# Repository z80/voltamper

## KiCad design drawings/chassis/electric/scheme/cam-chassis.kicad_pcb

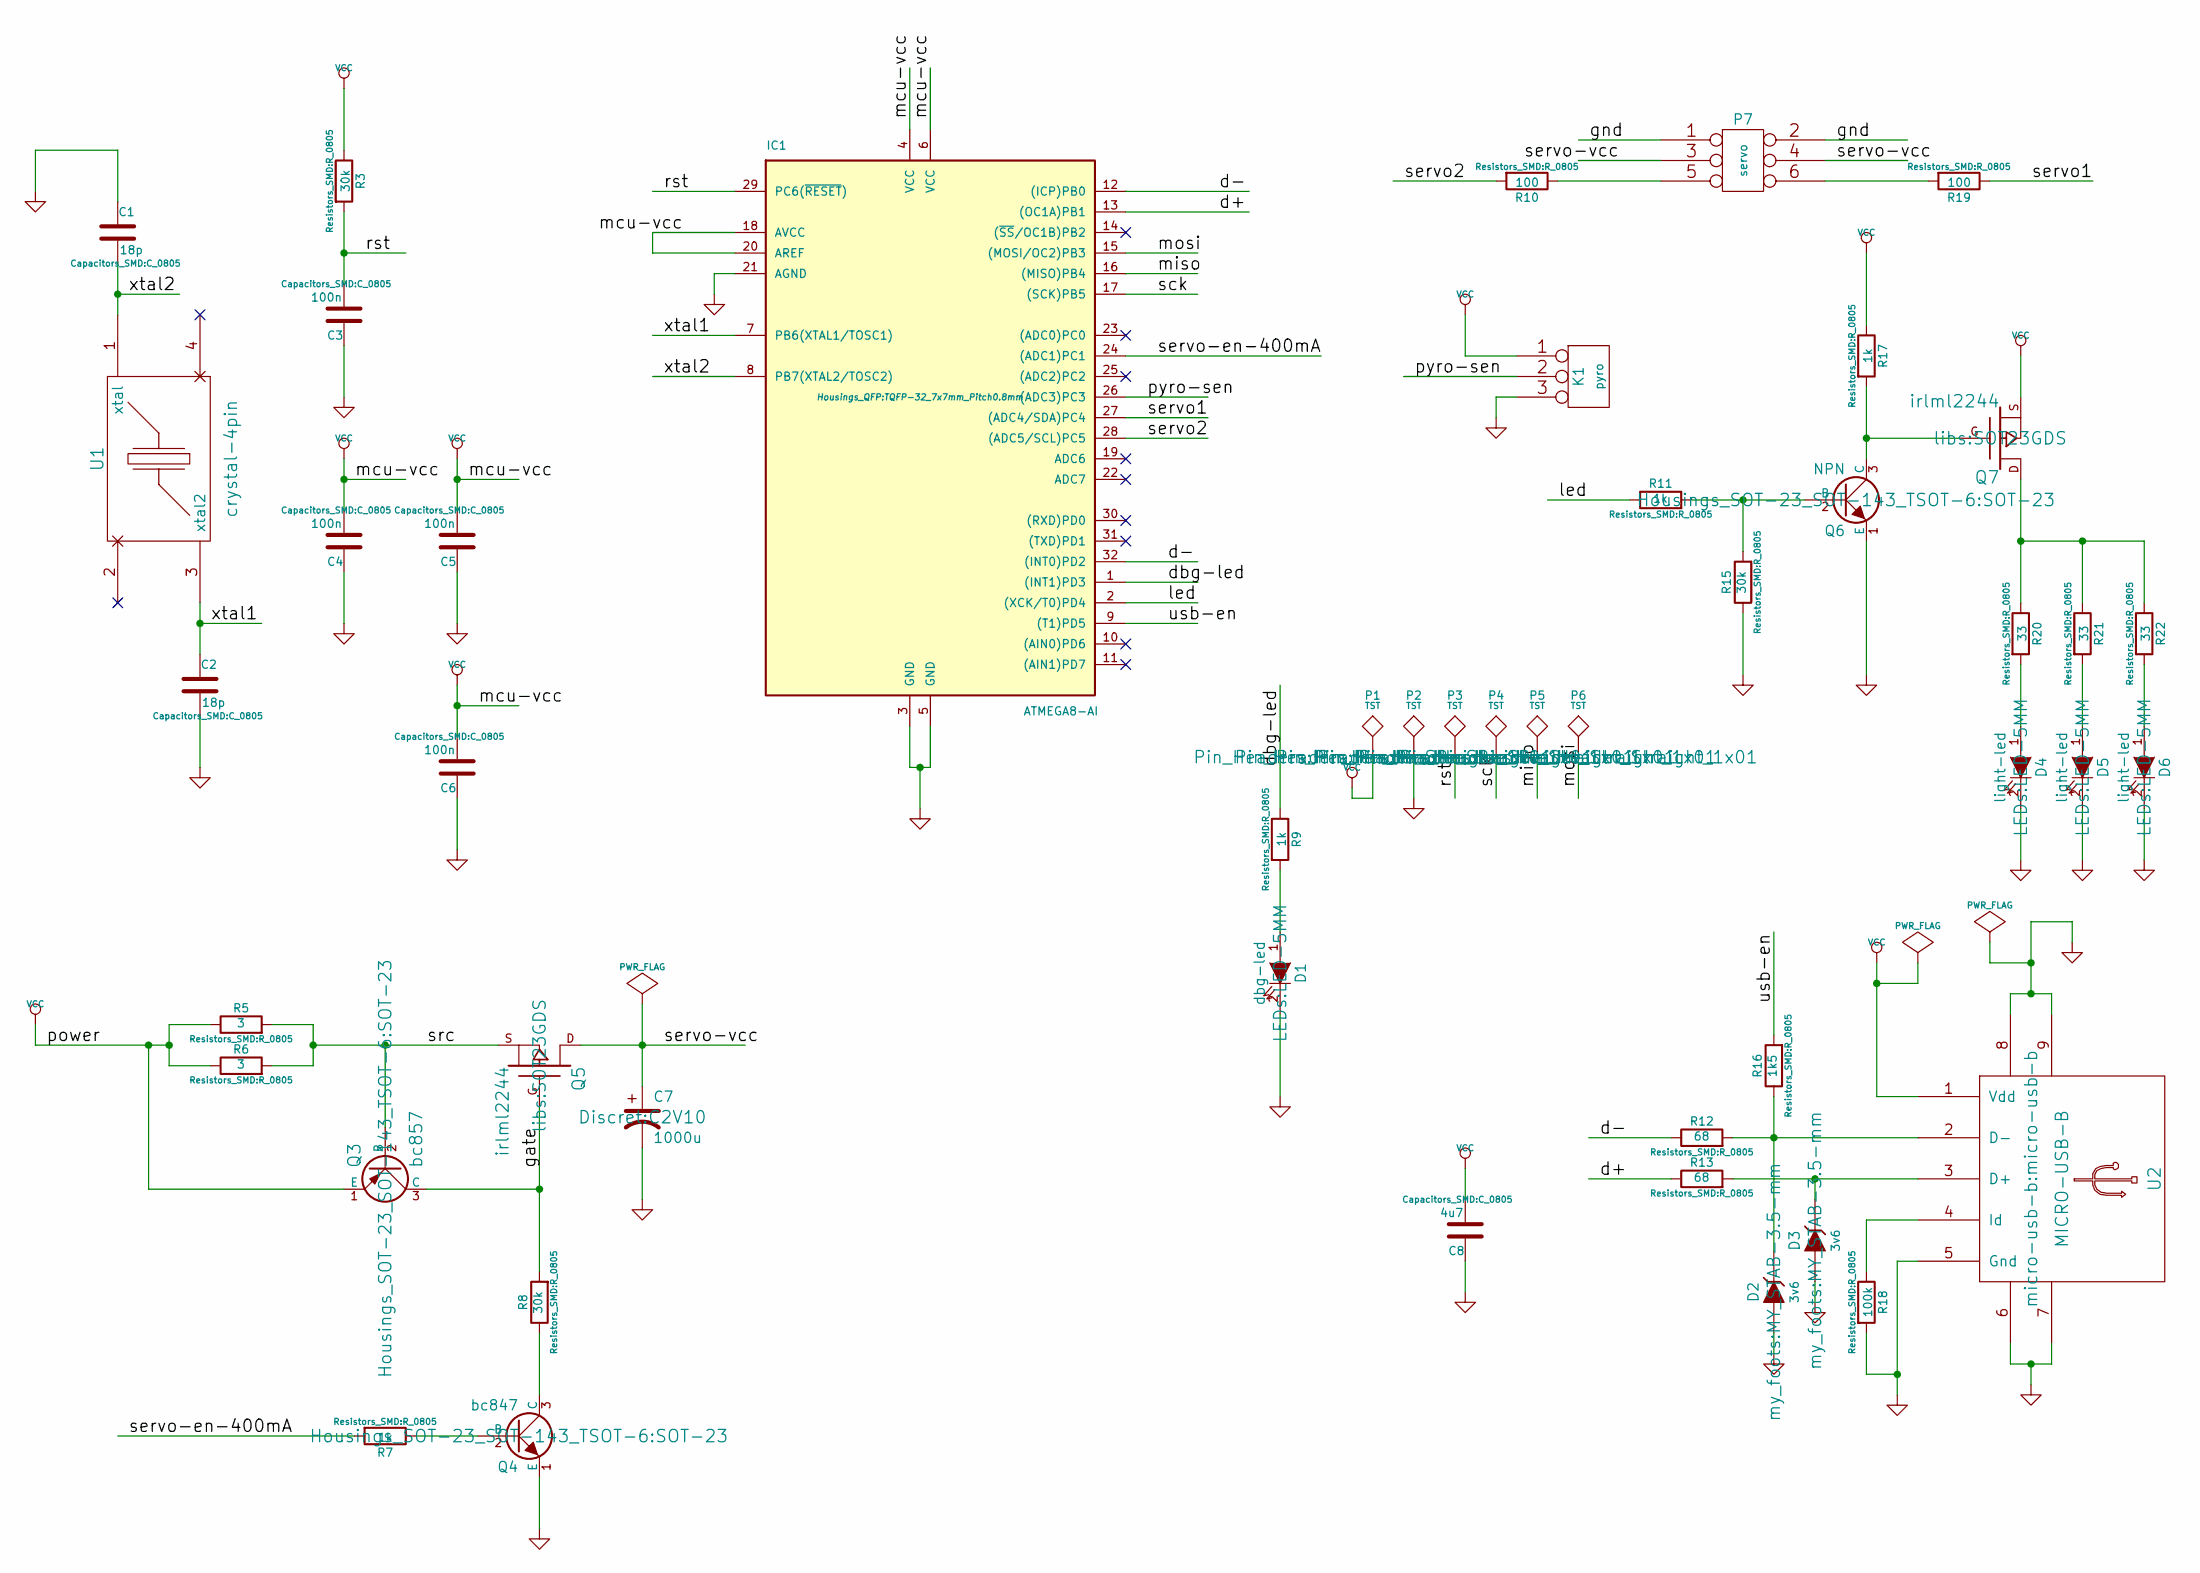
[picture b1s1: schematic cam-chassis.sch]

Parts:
C1, C2: 18p; C_0805
C3, C4, C5, C6: 100n; C_0805
C7: 1000u; C2V10
C8: 4u7; C_0805
D1: dbg-led; LED-5MM
D2, D3: 3v6; MY_STAB-3.5-mm
D4, D5, D6: light-led; LED-5MM
IC1: ATMEGA8-AI; TQFP-32_7x7mm_Pitch0.8mm
K1: pyro; Pin_Header_Straight_1x03
P1, P2, P3, P4, P5, P6: TST; Pin_Header_Straight_1x01
P7: servo; Pin_Header_Straight_2x03
Q3: bc857; SOT-23
Q4: bc847; SOT-23
Q5, Q7: irlml2244; SOT23GDS
Q6: NPN; SOT-23
R3, R8, R15: 30k; R_0805
R5, R6: 3; R_0805
R7, R9, R11, R17: 1k; R_0805
R10, R19: 100; R_0805
R12, R13: 68; R_0805
R16: 1k5; R_0805
R18: 100k; R_0805
R20, R21, R22: 33; R_0805
U1: crystal-4pin; CRYSTAL-SMD-5x3
U2: MICRO-USB-B; micro-usb-b

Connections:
/d+: IC1.13 ((OC1A)PB1), R13.1
/d-: IC1.12 ((ICP)PB0), IC1.32 ((INT0)PD2), R12.1
/dbg-led: IC1.1 ((INT1)PD3), R9.1
/gate: Q3.3 (C), Q5.G, R8.2
/led: IC1.2 ((XCK/T0)PD4), R11.1
/miso: IC1.16 ((MISO)PB4), P5.1
/mosi: IC1.15 ((MOSI/OC2)PB3), P6.1
/pyro-sen: IC1.26 ((ADC3)PC3), K1.2 (PM)
/rst: C3.2, IC1.29 (PC6(~RESET~)), P3.1, R3.2
/sck: IC1.17 ((SCK)PB5), P4.1
/servo1: IC1.27 ((ADC4/SDA)PC4), R19.1
/servo2: IC1.28 ((ADC5/SCL)PC5), R10.2
/servo-en-400mA: IC1.24 ((ADC1)PC1), R7.2
/servo-vcc: C7.1, P7.3, P7.4, Q5.D
/src: Q3.2 (B), Q5.S, R5.2, R6.2
/usb-en: IC1.9 ((T1)PD5), R16.2
/xtal1: C2.1, IC1.7 (PB6(XTAL1/TOSC1)), U1.3 (xtal2)
/xtal2: C1.2, IC1.8 (PB7(XTAL2/TOSC2)), U1.1 (xtal)
GND: C1.1, C2.2, C3.1, C4.1, C5.1, C6.1, C7.2, C8.1, D1.2 (K), D2.1 (A), D3.1 (A), D4.2 (K), D5.2 (K), D6.2 (K), IC1.3 (GND), IC1.5 (GND), IC1.21 (AGND), K1.3, P2.1, P7.1, P7.2, Q4.1 (E), Q6.1 (E), R15.1, R18.2, U2.5 (Gnd), U2.6, U2.7, U2.8, U2.9
unnamed: D1.1 (A), R9.2
unnamed: D2.2 (K), R12.2, R16.1, U2.2 (D-)
unnamed: D3.2 (K), R13.2, U2.3 (D+)
unnamed: D4.1 (A), R20.2
unnamed: D5.1 (A), R21.2
unnamed: D6.1 (A), R22.2
unnamed: P7.5, R10.1
unnamed: P7.6, R19.2
unnamed: Q4.2 (B), R7.1
unnamed: Q4.3 (C), R8.1
unnamed: Q6.2 (B), R11.2, R15.2
unnamed: Q6.3 (C), Q7.G, R17.2
unnamed: Q7.D, R20.1, R21.1, R22.1
unnamed: R18.1, U2.4 (Id)
VCC: C4.2, C5.2, C6.2, C8.2, IC1.4 (VCC), IC1.6 (VCC), IC1.18 (AVCC), IC1.20 (AREF), K1.1, P1.1, Q3.1 (E), Q7.S, R3.1, R5.1, R6.1, R17.1, U2.1 (Vdd)

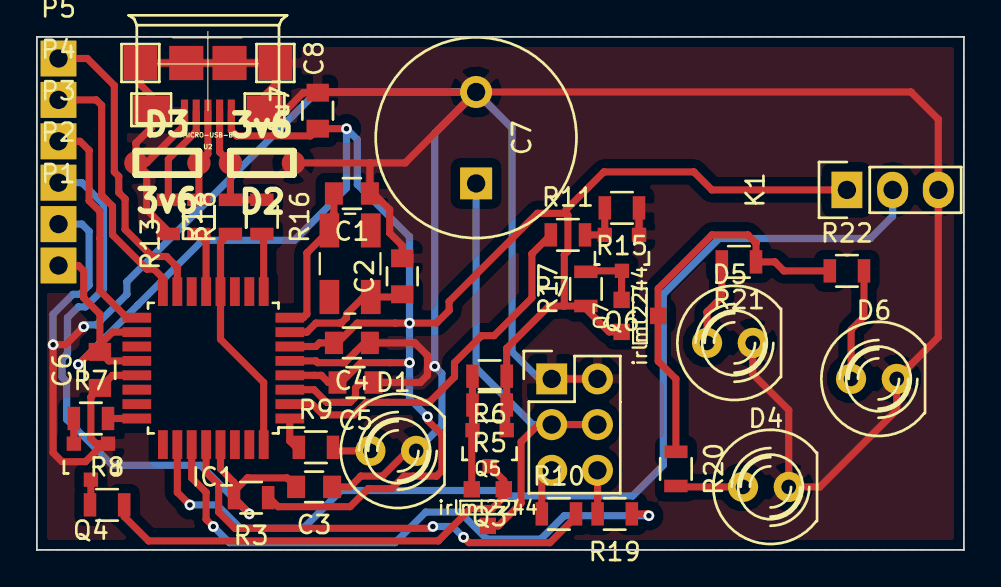
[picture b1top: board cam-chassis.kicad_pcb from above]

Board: 2 copper layers, 51.5 x 28.5 mm, 48 parts (0 on the bottom side), 34 nets.

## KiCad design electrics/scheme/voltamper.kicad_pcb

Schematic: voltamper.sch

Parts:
C1, C4, C5, C6, C9, C11, C13, C14, C19, C22, C28, C32, C34, C41: 100n
C2, C3: 18p
C7, C8, C10, C20, C23, C25, C26, C30, C35: 4u7
C12, C18: 1n
C15, C24, C36: 330u
C16, C17: 4u7
C21, C31: 2n2
C29, C33, C40: 30n
D1, D2, D3, D5, D6, D9: 1N5819
D10: led-0
D11: led-1
D12: led-2
K1: swd
K2: servo-1
K3: servo-2
L1, L2: 50uH
MCU1: STM32F100RCT6B
P1, P2: boot
P3: -
P4: +
P5: work
P6: aux
P7: ref
P8, P9, P10, P11: m3-hole
P12: CONN_13X2
Q1, Q3: bc857
Q2, Q4, Q8, Q9: bc847
Q5: irlml2244
R1, R4, R9, R15, R16, R17, R21, R26, R29, R47, R48, R49, R50, R51, R58, R59: 10k
R2, R5: 10k
R3, R23, R24: 100
R6: 100k
R7, R39, R67: 10
R8, R12, R20, R27, R31, R36, R41, R44, R45, R46, R52, R53, R54, R55, R63: 1k
R10, R11: 3
R13, R28: 0.15
R14, R34: 1k1
R18: 10k 0.1%
R25: 13.3k 0.1%
R30: 40k 0.1%
R32, R37, R42: 1k33
R33, R38, R43: 4k
R40: 5k3
R56, R57, R61, R62, R70, R71: 16
R60: 0
SW1: btn-1
SW2: btn-2
U1: CRYSTAL-4PIN
U2: CP2102
U3: MICRO-USB-B
U4, U5: MCP1703T-3302E/CB
U6, U8: NCP3063
U10: ADA4000
U11: INA126
U12, U15: SPARTAN-SIP-9007
U13: OPA551
U14: AD825

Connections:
/+: D1.1 (A), P4.1
/AVdd: C5.1, C17.1, MCU1.13 (Vdda), R18.1, R31.1, R36.1, R41.1, U5.2 (Vout)
/Eaux-in: C29.1, MCU1.8 (PC0-ADC_IN10), R31.2, R32.1, R33.1
/Eref: P7.1, U14.3 (in+), U15.1 (c1)
/Eref-in: C33.1, MCU1.9 (PC1-ADC_IN11), R36.2, R37.1, R38.1
/Iref: R43.2, U11.6 (Vd)
/Iref-in: C40.1, MCU1.10 (PC2-ADC_IN12), R41.2, R42.1, R43.1
/Vbus: D2.1 (A), U2.8 (Vbus), U3.1 (Vdd)
/Vin: C15.1, C19.1, C28.1, D1.2 (K), D2.2 (K), P12.17, P12.18, Q1.1 (E), Q3.1 (E), R7.1, R10.1, R11.1, R13.2, R28.2, U4.3 (Vin), U5.3 (Vin), U6.6 (vcc), U8.6 (vcc)
/aux-1: D9.1 (A), Q8.3 (C), U12.2 (in1)
/aux-en: MCU1.62 (PB9-TIM4_CH4-TIM17_CH1/I2C1_SDA(FT)), R27.1
/aux-pre: R39.1, R67.1, U11.2 (~Vin~), U12.1 (c1), U15.4 (c2)
/btn-1: MCU1.30 (PB11-I2C2_SDA-USART3_RX/TIM2_CH4(FT)), R47.2, SW1.2
/btn-2: MCU1.29 (PB10-I2C2_SCL-USART3_TX/TIM2_CH3/HDMI_C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), R48.2, SW2.2
/dac-high: MCU1.21 (PA5-SPI1_SCK-DAC_OUT2-ADC_IN5), R20.1
/dac-low: MCU1.20 (PA4-SPI1_NSS-USART2_CK-DAC_OUT1-ADC_IN4), R21.1
/eaux-volt: R33.2, R39.2, R67.2, U11.3 (Vin), U13.6
/eref-volt: C12.2, R38.2, R58.1, U14.2 (in-), U14.6 (out)
/f+: C20.1, R56.2, U10.5 (V+)
/f-: C23.1, R57.1, U10.2 (v-)
/gate: Q1.3 (C), Q3.3 (C), Q5.G, R9.2, R15.2
/gpio0: P12.25 (P24), P12.26 (P22), R52.2
/gpio1: P12.23, P12.24 (P20), R53.2
/gpio2: P12.21, P12.22, R54.2
/gpio3: P12.19, P12.20, R55.2
/i2c1-scl: MCU1.58 (PB6-I2C1_SCL-TIM4_CH1-TIM16_CH1N/USART1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), P12.5, P12.6, R49.2
/i2c1-sda: MCU1.59 (PB7-I2C1_SDA-FSMC_NADV-TIM4_CH2-TIM17_C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), P12.3, P12.4, R51.2
/led-0: D10.1 (A), MCU1.25 (PC5-ADC_IN15-TIM12_CH2)
/led-1: D11.1 (A), MCU1.26 (PB0-ADC_IN8-TIM3_CH3/TIM1_CH2N/TIM13_CH1)
/led-2: D12.1 (A), MCU1.27 (PB1-ADC)IN9-TIM3_CH4/TIM1_CH3N/TIM14_CH1)
/rxd: MCU1.42 (PA9-USART1_TX-TIM1_CH2-TIM15_BKIN(FT)), U2.25 (RXD)
/servo-1-pwm: MCU1.56 (PB4-NJTRST-SPI3_MISO/TIM3_CH1/SPI1-MISO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), R23.2
/servo-2-pwm: MCU1.57 (PB5-I2C1_SMBA-SPI3_MOSI-TIM16_BKIN/TIM3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), R24.2
/servo-en-60mA: MCU1.54 (PD2-TIM3_ETR-UART5_RX(FT)), R8.2
/servo-en-400mA: MCU1.55 (PB3-JTDO-SPI3_CLK/PB3/TRACESWO/TIM2_CH2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), R12.2
/servo-vcc: K2.2 (PM), K3.2 (PM), Q5.D
/short-1: D6.1 (A), Q9.3 (C), U15.2 (in1)
/short-en: MCU1.61 (PB8-TIM4_CH3-TIM16_CH1-HFMI_CEC/I2C1_SC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), R63.1
/src: Q1.2 (B), Q3.2 (B), Q5.S, R7.2, R10.2, R11.2
/suspend: MCU1.41 (PA8-USART1_CK-TIM1_CH1-MCO(FT)), U2.12 (SUSPEND)
/swd-clk: K1.3, MCU1.49 (PA14-JTCK-SWCLK(FT))
/swd-io: K1.1, MCU1.46 (PA13-JTMS-SWDIO(FT))
/txd: MCU1.43 (PA10-USART1_RX-TIM1_CH3-TIM17_BKIN(FT)), U2.26 (TXD)
/usart2-rx: MCU1.17 (PA3-USART2_RX-TIM5_CH3-ADC_IN3-TIM2_CH4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), P12.11, P12.12, R50.2
/usart2-tx: MCU1.16 (PA2-USART2_TX/TIM5_CH3-ADC_IN2-TIM15_CH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), P12.9, P12.10
/v+: C22.1, C24.1, C25.1, D3.2 (K), D6.2 (K), D9.2 (K), R16.2, R56.1, R61.1, R70.1, U12.3 (in2), U13.5, U15.3 (in2)
/v-: C26.1, C31.2, C32.1, C36.2, D5.1 (A), R34.2, R57.2, R62.2, R71.1, U8.4 (gnd), U13.4
GND: C1.2, C2.1, C3.1, C4.2, C6.2, C7.2, C8.2, C9.2, C10.2, C11.2, C13.2, C14.2, C15.2, C16.2, C19.2, C21.2, C22.2, C24.2, C28.2, C32.2, C36.1, K1.2 (PM), K2.3, K3.3, L2.1, MCU1.18 (Vss_4), MCU1.31 (Vss_1), MCU1.47 (Vss_2), MCU1.63 (Vss_3), P2.2 (PM), P3.1, P8.1, P9.1, P10.1, P11.1, P12.1, P12.2, P12.7, P12.8, P12.13, P12.14, Q2.1 (E), Q4.1 (E), Q8.1 (E), Q9.1 (E), R2.2, R5.2, R6.2, R14.2, R29.1, R44.2, R45.2, R46.2, R60.1, SW1.1, SW2.1, U1.2, U1.4, U2.0 (Gnd), U2.3 (Gnd), U3.5 (Gnd), U3.6, U3.7, U3.8, U3.9, U4.1 (Gnd), U6.2 (swe), U6.4 (gnd)
GNDA: C5.2, C17.2, C20.2, C23.2, C25.2, C26.2, C29.2, C30.2, C33.2, C34.2, C35.2, C40.2, C41.2, MCU1.12 (Vssa), P5.1, R17.2, R25.1, R26.2, R32.2, R37.2, R42.2, R60.2, U5.1 (Gnd), U11.5 (Gnd)
unnamed: C10.1, U2.18 (Vpp/nc)
unnamed: MCU1.28 (PB2/BOOT1(FT)), R5.1
unnamed: Q8.2 (B), R27.2
unnamed: P6.1, U12.4 (c2)
unnamed: MCU1.60 (BOOT0), P1.2 (PM), R2.1
unnamed: D10.2 (K), R44.1
unnamed: D11.2 (K), R45.1
unnamed: D12.2 (K), R46.1
unnamed: R26.1, R59.2, U13.1
unnamed: Q9.2 (B), R63.2
unnamed: C12.1, R17.1, R58.2, U13.2
unnamed: R20.2, R21.2, U10.3 (in+)
unnamed: C18.2, R30.1, R59.1, U10.1 (out)
unnamed: MCU1.36 (PB15-SPI2_MOSI-TIM1_CH3N-TIM15_CH1N/TIM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), R55.1
unnamed: MCU1.35 (PB14-SPI2_MISO-TIM1_CH2N-USART3_RTS/TIM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), R54.1
unnamed: MCU1.34 (PB13-SPI2_SCK-USART3_CTS-TIM1_CH1N/TIM1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), R53.1
unnamed: MCU1.33 (PB12-SPI2_NSS-I2C2_SMBA-USART3_CK-TIM1_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), R52.1
unnamed: C30.1, R61.2, U14.7 (v+)
unnamed: C18.1, R18.2, R25.2, R30.2, U10.4 (in-)
unnamed: C35.1, R62.1, U14.4 (v-)
unnamed: C1.1, R1.2, U2.9 (~RST~)
unnamed: U2.4 (D+), U3.3 (D+)
unnamed: U2.5 (D-), U3.2 (D-)
unnamed: R6.1, U3.4 (Id)
unnamed: R40.2, U11.1 (Rg2)
unnamed: R40.1, U11.8 (Rg1)
unnamed: C34.1, R70.2, U11.7 (V+)
unnamed: C41.1, R71.2, U11.4 (V-)
unnamed: MCU1.6 (OSC_OUT/PD1), R3.2
unnamed: C3.2, R3.1, U1.3
unnamed: C2.2, MCU1.5 (OSC_IN/PD0), U1.1
unnamed: C4.1, MCU1.7 (NRST), P2.1, R4.2
unnamed: Q4.3 (C), R15.1
unnamed: R29.2, R34.1, U8.5 (comp)
unnamed: K3.1, R24.1
unnamed: K2.1, R23.1
unnamed: Q4.2 (B), R12.1
unnamed: Q2.3 (C), R9.1
unnamed: Q2.2 (B), R8.1
unnamed: D5.2 (K), L2.2, U8.2 (swe)
unnamed: C21.1, U6.3 (tcap)
unnamed: L1.1, R13.1, U6.7 (ipk)
unnamed: R28.1, U8.1 (swc), U8.7 (ipk)
unnamed: C31.1, U8.3 (tcap)
unnamed: D3.1 (A), L1.2, U6.1 (swc)
unnamed: R14.1, R16.1, U6.5 (comp)
VDD: C6.1, C7.1, C8.1, C9.1, C11.1, C13.1, C14.1, C16.1, MCU1.1 (Vbat), MCU1.19 (Vdd_4), MCU1.32 (Vdd_1), MCU1.48 (Vdd_2), MCU1.64 (Vdd_3), P1.1, P12.15, P12.16, R1.1, R4.1, R47.1, R48.1, R49.1, R50.1, R51.1, U2.6 (Vdd), U2.7 (REGIN), U2.10 (nc), U2.13 (nc), U2.14 (nc), U2.15 (nc), U2.16 (nc), U2.17 (nc), U2.19 (nc), U2.20 (nc), U2.21 (nc), U2.22 (nc), U4.2 (Vout)

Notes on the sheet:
G=5+80k/Rg
Rg=6.8 => G=1+80/6.8 = 12.76
Just for compatibility with CP2109 and may be not installed for CP2102.
Servo controls.
USB scheme.
External IO socket.
+12V
-12V
Screw holes
-Vdd*4...+Vdd*4
Resistorsin different packages.

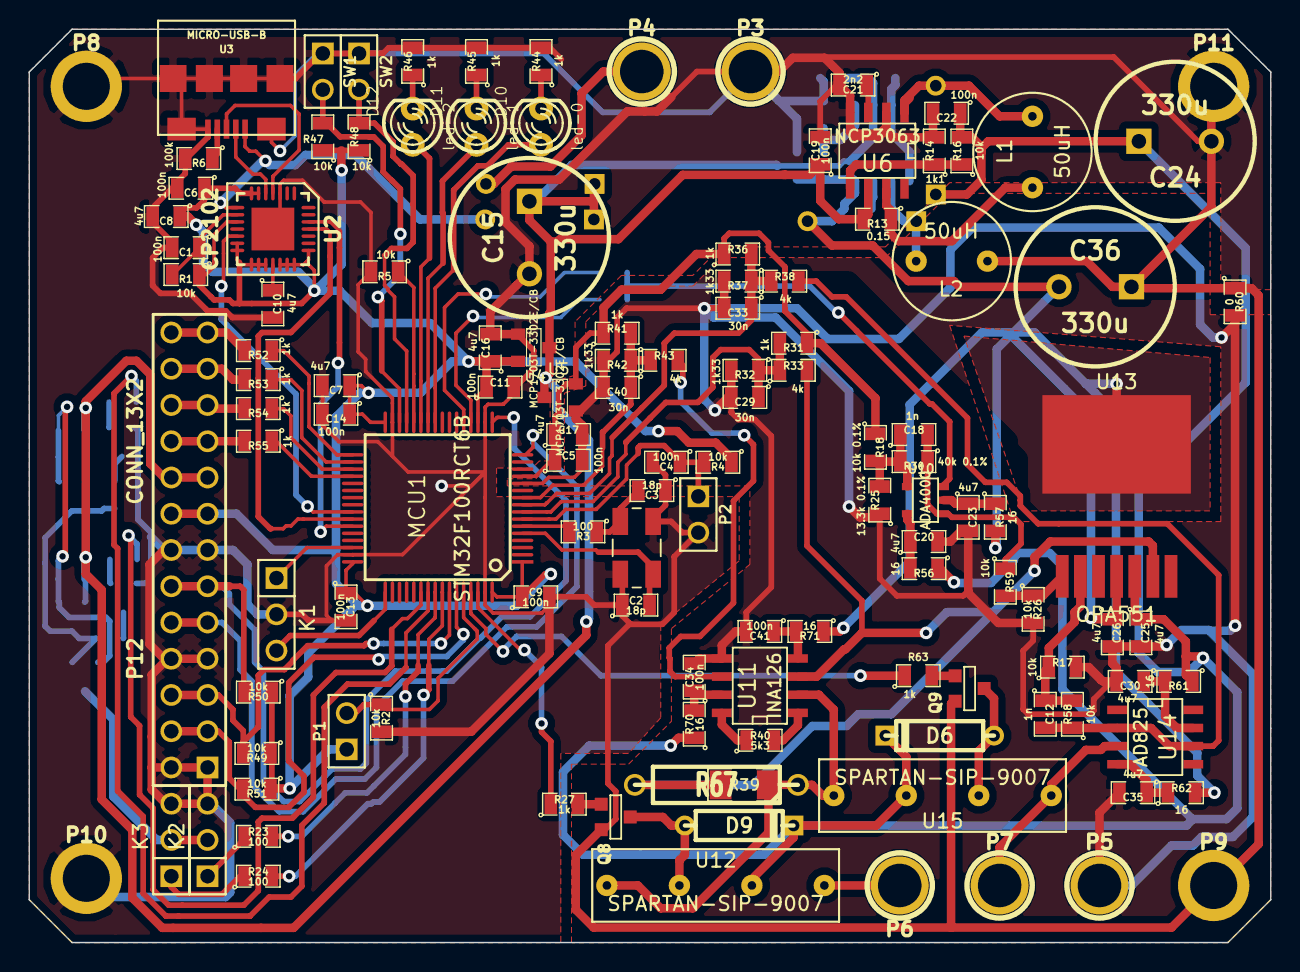
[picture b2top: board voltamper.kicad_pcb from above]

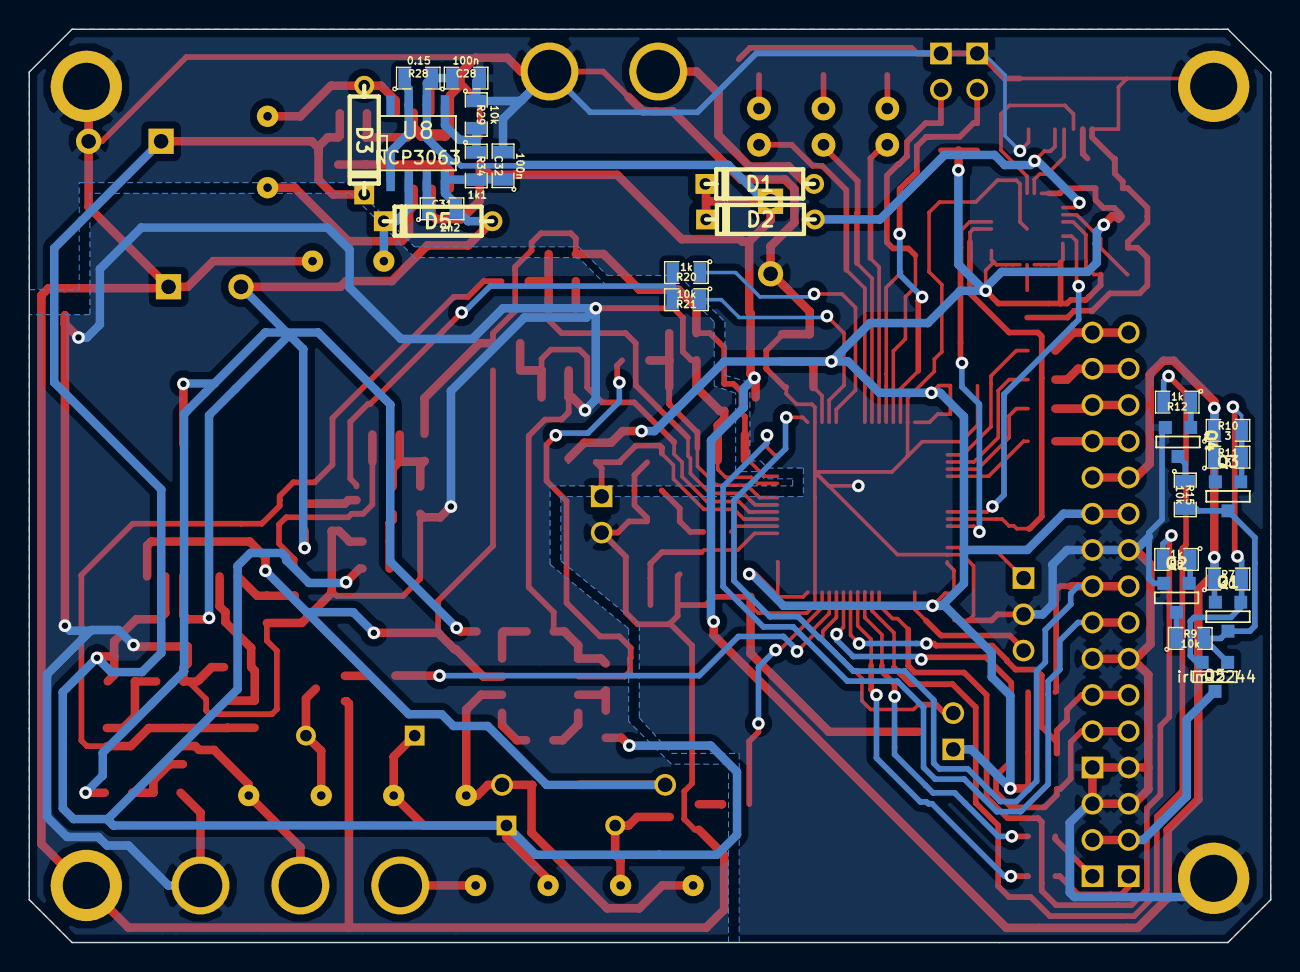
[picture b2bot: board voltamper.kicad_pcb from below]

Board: 2 copper layers, 87.0 x 64.0 mm, 149 parts (25 on the bottom side), 96 nets.

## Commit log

2014-12-04 Added docs.
2014-12-19 Finished but components lay too rarely. And board size is 10x10cm. It looks a little bit too large.
2014-12-19 Made wires wider.
2014-12-19 Gerbers and project for OSHPark.com.
2014-12-21 Started decreasing board size.
2014-12-21 Just exported gerber files.
2014-12-21 Generated correct files for OSHPark.
2014-12-22 Added software.
2014-12-23 Project compiles.
2014-12-23 Starting modifying scheme.
2014-12-24 Started changing scheme.
2014-12-24 About tot remove feedback buffer.
2014-12-29 Some PDFs about op amps stability are added. And a book "Op Amp for everyone".
2015-01-02 Very first modelling it works but it doesn't show any plots.
2015-01-02 Visualization works with Gaw.
2015-01-02 Op amp modelling works.
2015-01-04 Wasted entire day to understand that default value is "Log X = 1". Sh*t!
2015-01-04 Added INA126 SPICE model.
2015-01-04 Works with current feedback!!!
2015-01-04 almost adjusted original scheme. Modifying input op amp is left to do.
2015-01-05 Made footprint for opa551.
2015-01-05 Started placig components.
2015-01-06 In this way voltage feedback works properly.
2015-01-07 Experimenting with scheme.
2015-01-12 Placing elements. Finally decided to make software current feedback.
2015-01-12 Prepared gerbers. Needs extensions and file names adjustment.
2015-01-12 Prepared for OSHPark.
2015-01-12 Updated BOM.
2015-01-16 Adding BOM components to database.
2015-02-14 Added encoding and decoding.
2015-02-15 IO library compiles.
2015-02-17 Designing DAC modes.
2015-02-17 Firmware compiles without warnings.
2015-02-17 Added debug LED toggling from ADC ISR.
2015-02-17 Removed unused files.
2015-02-17 In the middle of implementing commands. But it's time to go to sleep...
2015-02-18 Inserted functions for external control.
2015-02-18 Made read method using TIMEOUT.
2015-02-18 Implemented reading until EOM or TIMEOUT.
2015-02-18 Implementing functions.
2015-02-18 Inserted mutex.
2015-02-19 Started GUI application.
2015-02-20 Implementing GUI software.
2015-02-21 Designing GUI...
2015-02-23 Designing user interface.
2015-02-24 Made GUI software part.
2015-02-25 Started calibration implementation.
2015-03-06 Fixed a few points in calibration and in all other stuff.
2015-03-06 Checked calibration. It turned out that "index++" in GCC works not in the same way as in MSVC. I had to change matrix2.hpp source code.
2015-03-06 Commented debug code.
2015-03-08 Started housing.
2015-03-08 Looks like ready to make lower part.
2015-03-08 Case looks done.
2015-03-10 Added sweep functionality.
2015-03-10 Inserted sweep window and sweep functionality. Not tested yet.
2015-03-18 Gear generation macros save.
2015-03-25 AT90USB162 documentation.
2015-04-19 Done with routing.
2015-04-29 Added enforcements to housing.
2015-05-04 Made cuts in case bottom.
2015-05-22 Housing printing
2015-05-23 Elchem filter design.
2015-05-24 Modelling and some docs.
2015-05-24 ADC and filter opamp for elchem.
2015-05-28 Doc about bias current.
2015-06-11 Failed to update qextserialport.
2015-06-13 Turned event driven off.
2015-06-13 Debugging read.
2015-06-15 Write back form the firmware works.
2015-06-16 Working on it. Debugging setDac. Any value cause dac to be at maximum.
2015-06-17 Changed indexed array into switch-case.
2015-06-18 Debugging...
2015-06-19 Found a mistake in amplifier range calculation (!!!)
2015-06-20 Added filtering to oscilloscope measures.
2015-06-22 Added a few icons.
2015-06-22 Have to comment this out to prevent failures on software exit.
2015-06-26 Voltage data.
2015-06-26 Killed mean value biasing in oscilloscope.
2015-06-26 Proved linear model in this case is the best one.
2015-06-26 Modified case.
2015-06-26 Adjusted title.
2015-06-29 Fixed a few troubles.
2015-07-01 Fixed stopping script execution.
2016-02-22 Started buffer for parametric measures.
2016-02-23 Have been designing buffer.
2016-03-05 Wes implementing circular buffer.
2016-03-05 Prepared functions and firmware. Also need to remake GUI to use buffer rather then oscilloscope.
2016-03-06 Inserted Into GUI. But didn't check how it works.
2016-03-07 Inserted buffer period adjustment to meandr, sweep and single pulse.
2016-03-15 Removed special buffer. Incorporated oscilloscope start by start of sweep.
2016-03-15 Debugging drawing functionality.
2016-03-15 Fixed drawing. Now it runs but result isn't exactly what was expected. Especially if period isn't large.
2016-03-16 Implemented oscStopped() function.
2016-03-16 Implemebted continuous and stoppable oscilloscope.
2016-03-17 Debugging periodic replots.
2016-03-17 At least now it's in one and the same place.
2016-03-17 Merged stashed changes.
2016-03-17 Speeded up ADC.
2016-07-06 Made current feedback.
2016-07-06 Changed firmrare version to 0.0.2.
2016-07-07 Increased font size. Added coulombs measurement.
2016-07-14 Number of improvements.
2016-10-07 Written down all corrections (right on SCH) made to improve the thing.
